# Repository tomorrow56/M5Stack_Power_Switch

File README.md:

# M5Stack_Power_Switch

Add a physical switch to disconnect the battery.

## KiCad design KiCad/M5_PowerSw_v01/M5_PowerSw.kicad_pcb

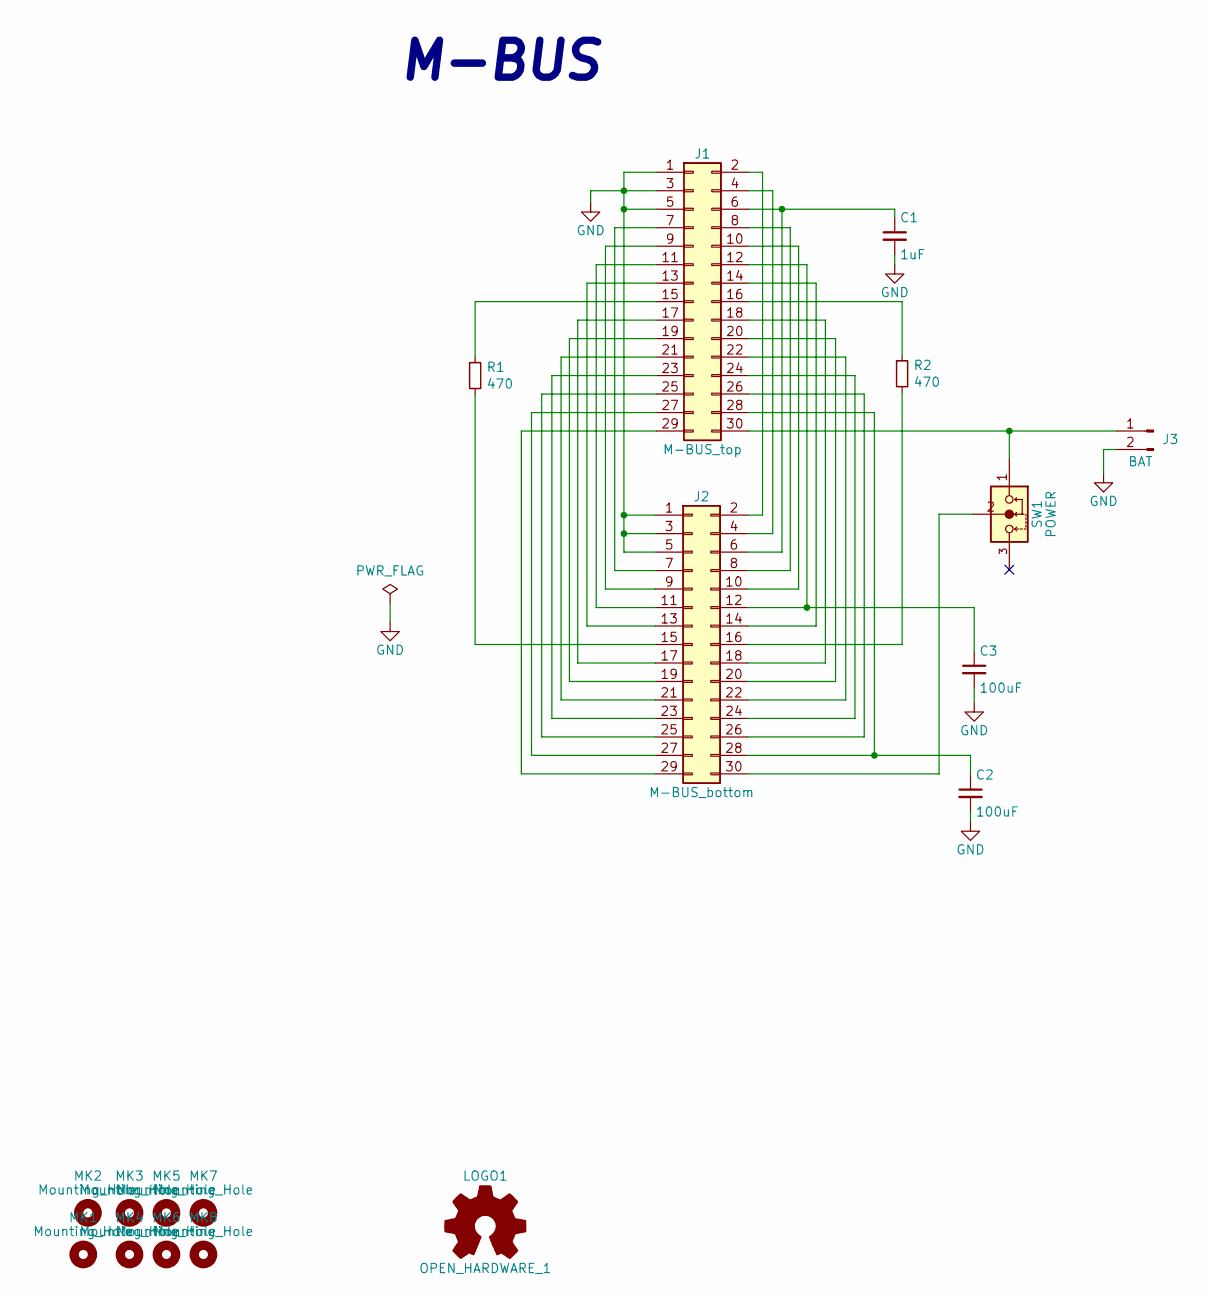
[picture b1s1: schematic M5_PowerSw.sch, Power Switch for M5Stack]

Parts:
C1: 1uF; C_0603_1608Metric
C2, C3: 100uF; C_1206_3216Metric
J1: M-BUS_top; Pin_Header_MBUS_SMD_top
J2: M-BUS_bottom; Pin_Header_MBUS_SMD_bottom
J3: BAT; PinHeader_1x02_P2.54mm_Horizontal
LOGO1: OPEN_HARDWARE_1; OSHW-Logo_5.7x6mm_SilkScreen
MK1, MK2, MK3, MK4: Mounting_Hole; MountingHole_3.2mm_M3
MK5, MK6, MK7, MK8: Mounting_Hole; MountingHole_2.2mm_M2
R1, R2: 470; R_0603_1608Metric
SW1: POWER; slide_switch_angled

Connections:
GND: C1.2, C2.2, C3.2, J1.1, J1.3, J1.5, J2.1, J2.3, J2.5, J3.2
unnamed: C1.1, J1.6, J2.6
unnamed: C2.1, J1.28, J2.28
unnamed: C3.1, J1.12, J2.12
unnamed: J1.2, J2.2
unnamed: J1.4, J2.4
unnamed: J1.7, J2.7
unnamed: J1.8, J2.8
unnamed: J1.9, J2.9
unnamed: J1.10, J2.10
unnamed: J1.11, J2.11
unnamed: J1.13, J2.13
unnamed: J1.14, J2.14
unnamed: J1.15, R1.1
unnamed: J1.16, R2.1
unnamed: J1.17, J2.17
unnamed: J1.18, J2.18
unnamed: J1.19, J2.19
unnamed: J1.20, J2.20
unnamed: J1.21, J2.21
unnamed: J1.22, J2.22
unnamed: J1.23, J2.23
unnamed: J1.24, J2.24
unnamed: J1.25, J2.25
unnamed: J1.26, J2.26
unnamed: J1.27, J2.27
unnamed: J1.29, J2.29
unnamed: J1.30, J3.1, SW1.1
unnamed: J2.15, R1.2
unnamed: J2.16, R2.2
unnamed: J2.30, SW1.2

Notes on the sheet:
M-BUS

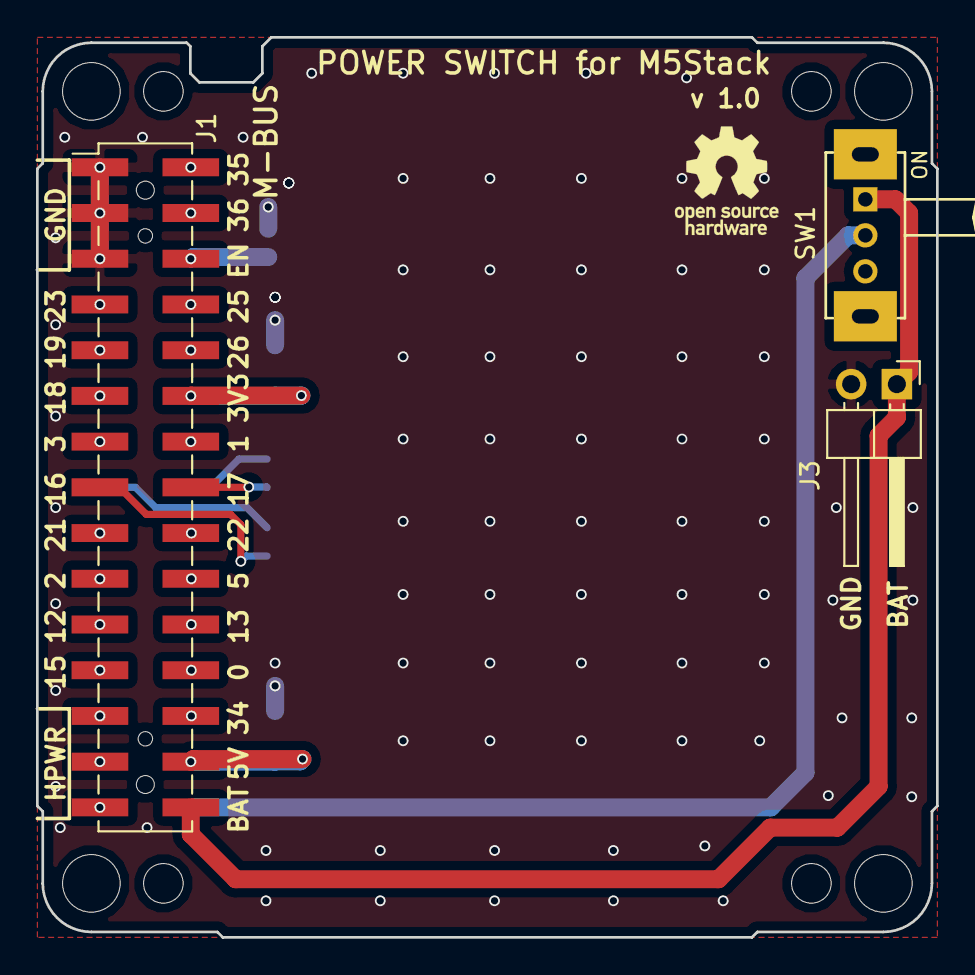
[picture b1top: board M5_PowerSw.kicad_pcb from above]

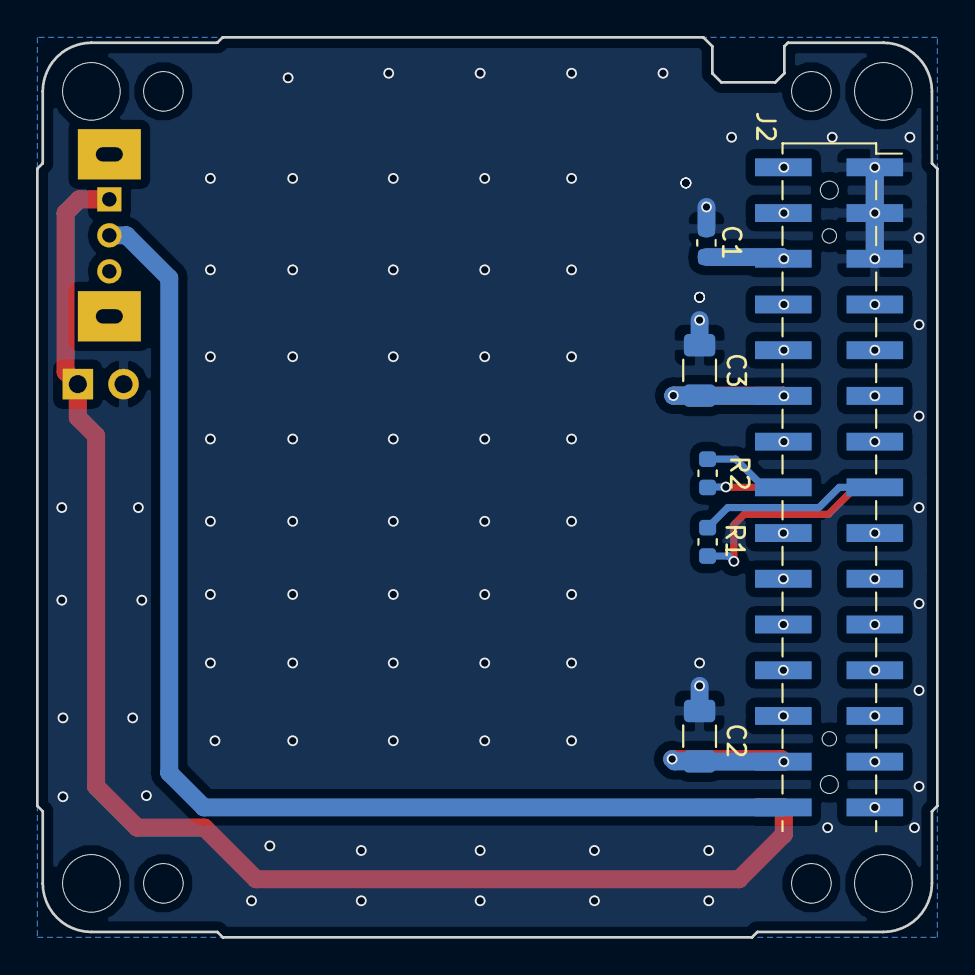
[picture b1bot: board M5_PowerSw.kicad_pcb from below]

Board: 2 copper layers, 50.0 x 50.0 mm, 18 parts (5 on the bottom side), 31 nets.

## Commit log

2020-03-13 add schemarics
